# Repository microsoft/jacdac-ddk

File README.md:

> [!IMPORTANT]
> This repository has moved to https://github.com/jacdac/jacdac-ddk 

# Jacdac Device Development Kit (DDK) Reference Materials

## Introduction

This repository contains reference materials for creators of [Jacdac](https://aka.ms/jacdac) devices. More specifically, it has technical drawings, part libraries and device designs (schematics and layout files). In conjunction with the [Jacdac device design documentation](https://microsoft.github.io/jacdac-docs/ddk/) and our [Jacdac firmware repositories](https://microsoft.github.io/jacdac-docs/ddk/firmware/), these materials form the Jacdac device design kit (DDK). The DDK contains everything necessary to design and manufacture [Jacdac devices](https://microsoft.github.io/jacdac-docs/devices/).

Please also refer to discussions at https://github.com/microsoft/jacdac/discussions and note that issues are tracked on https://github.com/microsoft/jacdac/issues.

## Repository structure

-   `/connector`: specification of the Jacdac PCB connector, cable connector and cable assemblies;
-   `/electronics`: reference materials and implementations of different types of device in the form of schematics, layouts and parts libraries for various electronics CAD packages;
-   `/enclosures`: files relating to enclosures for Jacdac modules and devices; and
-   `/graphics`: image files that might be useful for device design, packaging and/or marketing materials.

Note that the contents of any files under a `deprecated_form_factor` or `explorations` folder are provided for interest only, these should not be considered reference material relating to the Jacdac standard.

## Contributing to Jacdac

This project welcomes contributions and suggestions. Most contributions require you to agree to a
Contributor License Agreement (CLA) declaring that you have the right to, and actually do, grant us
the rights to use your contribution. For details, visit https://cla.opensource.microsoft.com.

When you submit a pull request, a CLA bot will automatically determine whether you need to provide
a CLA and decorate the PR appropriately (e.g., status check, comment). Simply follow the instructions
provided by the bot. You will only need to do this once across all repos using our CLA.

This project has adopted the [Microsoft Open Source Code of Conduct](https://opensource.microsoft.com/codeofconduct/).
For more information see the [Code of Conduct FAQ](https://opensource.microsoft.com/codeofconduct/faq/) or
contact [opencode@microsoft.com](mailto:opencode@microsoft.com) with any additional questions or comments.

## Legal Notices

Microsoft and any contributors grant you a license to the Microsoft documentation and other content
in this repository under the [Creative Commons Attribution 4.0 International Public License](https://creativecommons.org/licenses/by/4.0/legalcode),
see the [LICENSE](LICENSE) file, and grant you a license to any code in the repository under the [MIT License](https://opensource.org/licenses/MIT), see the
[LICENSE-CODE](LICENSE-CODE) file, and grant you a license to any hardware designs in the repository under the [CERN Open License v2](https://opensource.org/license/cern-ohl-p), see the [LICENSE-HARDWARE](LICENSE-HARDWARE) file.

Use of this open hardware project, as well as any physical hardware created using it, carries risks of malfunction or failure. It is not subject to the same testing and quality control as designs created for products to be put into commerce and may not be suitable for mission-critical, high-risk applications, or other uses where failure could result in personal injury, death, property damage, other harm or loss including but not limited to data loss or corruption. By using this project or any hardware created using it, you assume all risks and agree to not hold its creators or distributors responsible for any damages or losses resulting from that use.

Microsoft, Windows, Microsoft Azure and/or other Microsoft products and services referenced in the documentation
may be either trademarks or registered trademarks of Microsoft in the United States and/or other countries.
The licenses for this project do not grant you rights to use any Microsoft names, logos, or trademarks.
Microsoft's general trademark guidelines can be found at http://go.microsoft.com/fwlink/?LinkID=254653.

Privacy information can be found at https://privacy.microsoft.com/en-us/

Microsoft and any contributors reserve all other rights, whether under their respective copyrights, patents,
or trademarks, whether by implication, estoppel or otherwise.

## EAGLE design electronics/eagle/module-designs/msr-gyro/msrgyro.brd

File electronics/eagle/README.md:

# Jacdac library and reference designs for Eagle

This folder contains a Jacdac library for Eagle and an example module reference design. We plan to have more Eagle Jacdac design examples in due course.

Notes:
* there are tDocu layer lines indicating keepout areas as per the [EC30 spec](https://microsoft.github.io/jacdac-docs/ddk/design/ec30/);
  that keepout applies to components not traces or test points
* the traces connecting power nets (GND and JD_PWR) between multiple Jacdac
  connectors and mounting holes should be at least 12mil/0.3mm to allow 1A to flow through them
* to make the board bigger, set the grid to 10mm, select half the board and use the MOVE tool
* if you remove the connector on the right hand side the keepout area no longer applies on that side
* left hand side should not be removed
* the board has a number of traces locked; you can rip out all the other traces and run the auto-router
* try to keep the trace from JD pin to FB1 short to improve EMC
* ESD protection diodes may not be necessary for prototyping

The `gerber.zip` file(s) contain exported Gerber layers as well as BOM and PNP files suitable for JLCPCB.

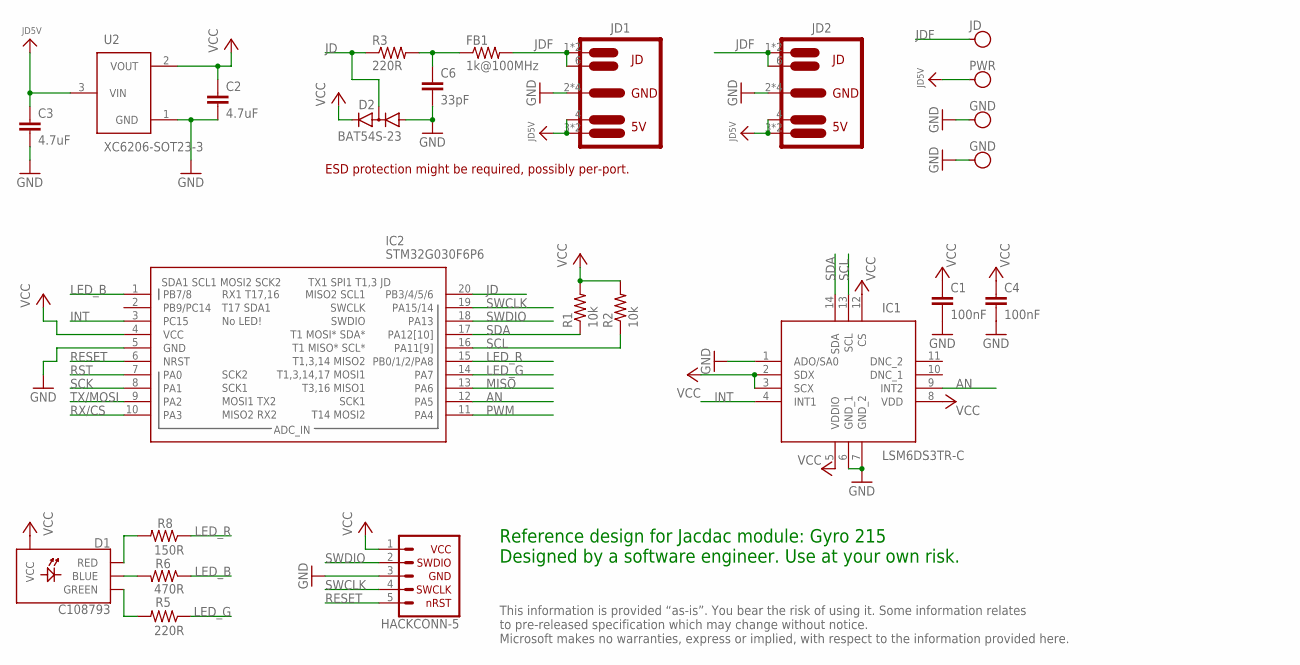
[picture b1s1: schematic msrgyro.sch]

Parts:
C1, C4: 100nF; 0402
C2, C3: 4.7uF; 0402
C6: 33pF; 0402
D1: C108793; LED-RGB-2020
D2: BAT54S-23; SOT23-3
FB1: 1k@100MHz; 0402
IC1: LSM6DS3TR-C; LGA-14-2.5_3
IC2: STM32G030F6P6; SOP65P640X120-20N
J1: JD; M3-HOLE-DATA
J2: PWR; M3-HOLE-PWR
J3, J4: GND; M3-HOLE-GND
J6: HACK-CONNECT-5; HC5-22-62
JD1, JD2: JACDAC-EDGE-OUTIE; JD-EDGE-OUTIE
R1, R2: 10k; 0402
R3, R5: 220R; 0402
R6: 470R; 0402
R8: 150R; 0402
U2: XC6206-SOT23-3; SOT23-3-W

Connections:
AN: IC1.9 (INT2), IC2.12 (PA5)
GND: C1.2, C2.2, C3.2, C4.2, C6.2, D2.1 (A1), IC1.1 (ADO/SA0), IC1.6 (GND_1), IC1.7 (GND_2), IC2.5 (GND), J3.H, J4.H, J6.3 (GND), JD1.2 (1), JD1.5 (1), JD1.P$2 (1), JD1.P$4 (1), JD2.2 (1), JD2.5 (1), JD2.P$2 (1), JD2.P$4 (1), U2.1 (GND)
INT: IC1.4 (INT1), IC2.3 (PC15)
JD: D2.3 (C1A2), IC2.20 (PB3/4/5/6), R3.1
JD5V: C3.1, J2.H, JD1.3, JD1.4, JD1.P$1 (3), JD2.3, JD2.4, JD2.P$1 (3), U2.3 (VIN)
JDF: FB1.2, J1.H, JD1.1 (2), JD1.6, JD1.P$3 (2), JD2.1 (2), JD2.6, JD2.P$3 (2)
LED_B: IC2.1 (PB7/8), R6.1
LED_G: IC2.14 (PA7), R5.1
LED_R: IC2.15 (PB0/1/2/PA8), R8.1
MISO: IC2.13 (PA6)
unnamed: C6.1, FB1.1, R3.2
unnamed: D1.B- (BLUE), R6.2
unnamed: D1.R- (RED), R8.2
unnamed: D1.G- (GREEN), R5.2
PWM: IC2.11 (PA4)
RESET: IC2.6 (NRST), J6.5 (NRST)
RST: IC2.7 (PA0)
RX/CS: IC2.10 (PA3)
SCK: IC2.8 (PA1)
SCL: IC1.13 (SCL), IC2.16 (PA11[9]), R2.1
SDA: IC1.14 (SDA), IC2.17 (PA12[10]), R1.1
SWCLK: IC2.19 (PA15/14), J6.4 (SWCLK)
SWDIO: IC2.18 (PA13), J6.2 (SWDIO)
TX/MOSI: IC2.9 (PA2)
VCC: C1.1, C2.1, C4.1, D1.PLUS (VCC), D2.2 (C2), IC1.2 (SDX), IC1.3 (SCX), IC1.5 (VDDIO), IC1.8 (VDD), IC1.12 (CS), IC2.4 (VCC), J6.1 (VCC), R1.2, R2.2, U2.2 (VOUT)

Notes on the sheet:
Reference design for Jacdac module: Gyro 215 Designed by a software engineer. Use at your own risk.
This information is provided “as-is”. You bear the risk of using it. Some information relates to pre-released specification which may change without notice. Microsoft makes no warranties, express or implied, with respect to the information provided here.
ESD protection might be required, possibly per-port.

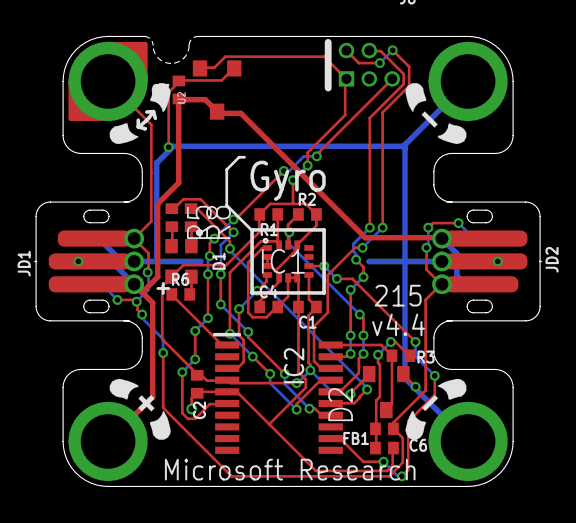
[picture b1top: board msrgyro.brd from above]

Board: 2 copper layers, 28.0 x 25.0 mm, 24 parts (0 on the bottom side), 19 nets.

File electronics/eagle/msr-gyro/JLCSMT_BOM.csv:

Comment,Designator,Footprint,LCSC Part#
"CAP_0402 4.7uF","C3","0402","C23733"
"CAP_0402 4.7uF","C2","0402","C23733"
"RES_0402 220R","R3","0402","C25091"
"CAP_0402 33pF","C6","0402","C1562"
"RES_0402 1k@100MHz","FB1","0402","C21516"
"XC6206-SOT23-3","U2","SOT-23-3L","C5446"
"LED-RGB-CA-2020 C108793","D1","LED-4_2020","C108793"
"RES_0402 470R","R6","0402","C25117"
"RES_0402 150R","R8","0402","C25082"
"RES_0402 220R","R5","0402","C25091"
"BAT54S-23 BAT54S-23","D2","SOT-23","C408389"
"STM32G030F8P6 STM32G030F6P6","IC2","TSSOP-20","C724040"
"RES_0402 10k","R1","0402","C25744"
"RES_0402 10k","R2","0402","C25744"
"LSM6DS3TR-C LSM6DS3TR-C","IC1","LGA-14","C967633"
"CAP_0402 100nF","C1","0402","C1525"
"CAP_0402 100nF","C4","0402","C1525"

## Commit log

2020-12-16 Initial LICENSE commit
2020-12-16 Initial CODE_OF_CONDUCT.md commit
2020-12-16 Initial LICENSE-CODE commit
2020-12-16 Initial README.md commit
2020-12-16 Initial SECURITY.md commit
2020-12-16 adding connector folder
2020-12-16 Update README.md
    Adding title
2020-12-16 added PCB edge connector drawing
2020-12-16 using underscores in pdf names
2020-12-16 add connector
2020-12-16 updated link
2020-12-16 link to folder
2020-12-16 add link to pdf
2020-12-16 link to jacdac
2020-12-16 Link firmware repos
2020-12-16 bring over text from word doc
2020-12-16 add link to devices
2020-12-16 components
2020-12-16 add more structure
2020-12-17 Rename and link connector PDF
2020-12-17 typos corrected
2021-02-12 add a page for module submission
2021-02-16 Explain about pin order
2021-02-16 resize image
2021-02-16 resizing doesn't work
2021-02-16 another attempt at sizing
2021-02-16 simpler path for image
2021-02-23 rename JACDAC to Jacdac
2021-04-06 MDK -> DDK
2021-04-06 header
2021-04-06 jacdac-ts -> jacdac-docs
2021-04-06 remove extra
2021-04-06 remove module
2021-04-06 typos
2021-04-06 three features, just three!
2021-04-06 typo fixed
2021-04-07 host -> server
2021-04-07 small update
2021-05-03 updated README.md
    Broadened scope to include power supplies and Jacdaptors in addition to modules and brains.
    Highlighted the existence of dedicated vs. integrated brains.
    Re-structured to improve flow.
    Refined text throughout.
2021-05-03 Update README.md
    Added motivation that's consistent with other Jacdac docs.
2021-05-03 Update README.md
    Initial draft underway.
2021-05-03 Update README.md
    Continuing with first draft.
2021-05-07 Add firmware page and link it
2021-05-24 JACDAC -> Jacdac
2021-06-30 test commit from VS Code
2021-07-02 Revised hardware design guidelines
2021-07-15 updated PCB edge connecter dwg, refined text
2021-07-23 more edits
2021-07-26 add reference design and notes
2021-07-26 remote outdated descs
2021-07-26 cleanup footprint reradme
2021-07-26 pictures
2021-07-26 cleanup + schematic
2021-07-26 lol ouch
2021-08-06 partner preview message
2021-08-13 Rename JD-PEC-01 to JC-PEC-02
2021-08-13 update stragglers
2021-08-13 Update JLCPCB Part #
2021-08-13 words
2021-08-13 grammar
2021-08-13 words, again
2021-09-10 don't point to beta editor
2021-09-11 Adding EAGLE Jacdac footrpitns and design blocks
2021-09-11 syntax
2021-12-01 reorg design folders
2021-12-01 rename library => libraries; add subfolders to altium
2021-12-01 update slider file references
2021-12-02 add Jacdac.IntLib under altium
2021-12-02 updates to docs for public release
2021-12-02 adding link to the QR code generator for devices
2021-12-02 remove duplicated markdown
2021-12-02 typo
2021-12-02 more cleanup
2021-12-03 updated folder name
2021-12-03 Add Rotary and Temp+Humidity reference designs
2021-12-03 Add micro:bit Jacdapter reference design
2021-12-03 Add RGBLedRing reference design
2021-12-03 Add G0 Button reference design
2021-12-03 removing extra electronics/readme file
2021-12-20 Add accelerometer reference design
2021-12-20 Add generic RGB LED strip reference design
2021-12-20 Add padauk light level sensor reference design
2021-12-21 Add padauk analog joystick reference design
2021-12-21 Remove status report text files
2022-01-10 Add Access Switch Input 1.4
2022-01-11 link to jacdac issues
2022-02-07 updated qr code generator link
2022-02-17 fix links
2022-05-26 move old designs to deprecated_form_factor
2022-05-27 adding graphics
2022-06-06 ec30 pdf
2022-06-12 Add MSR Gyro board reference design
2022-06-13 Update README.md
    add link to EC30 spec
2022-06-13 rotate LSM6D to match JLC spec
2022-06-13 add printout of schematics
2022-06-13 ignore generated eagle files
2022-06-13 add generated files
2022-06-14 additions to DDK
2022-06-14 updating reference CAD files
2022-06-15 renamed folder
2022-06-15 fixed typos
2022-06-15 adding altium reference designs
2022-06-16 improved introduction
2022-06-16 updated suggested components
2022-06-16 added current limiters
2022-06-16 added component details
2022-06-16 edits to schottky diode table
2022-06-17 remove old files
2022-06-17 use aka.ms links in readme
2022-06-17 updated altium edge connector reference design
2022-06-17 added altium module reference designs
2022-06-21 fix connector size in EAGLE library
2022-06-21 update size of the jacdac connector in EAGLE design
2022-06-21 add generated gerber and BOM/PNP
2022-06-26 added ref schematics, cable connector STEP, diode
2022-06-27 edit to readme
2022-07-25 adding Jacdac cable extender design files
2022-08-15 added push buttons, USB C connectors, crystals
2023-09-14 adding RP2040 brain
2023-10-13 adding miscellaneous design files
2025-03-19 add CERN
2025-03-19 renaming
2025-08-13 move to jacdac org
